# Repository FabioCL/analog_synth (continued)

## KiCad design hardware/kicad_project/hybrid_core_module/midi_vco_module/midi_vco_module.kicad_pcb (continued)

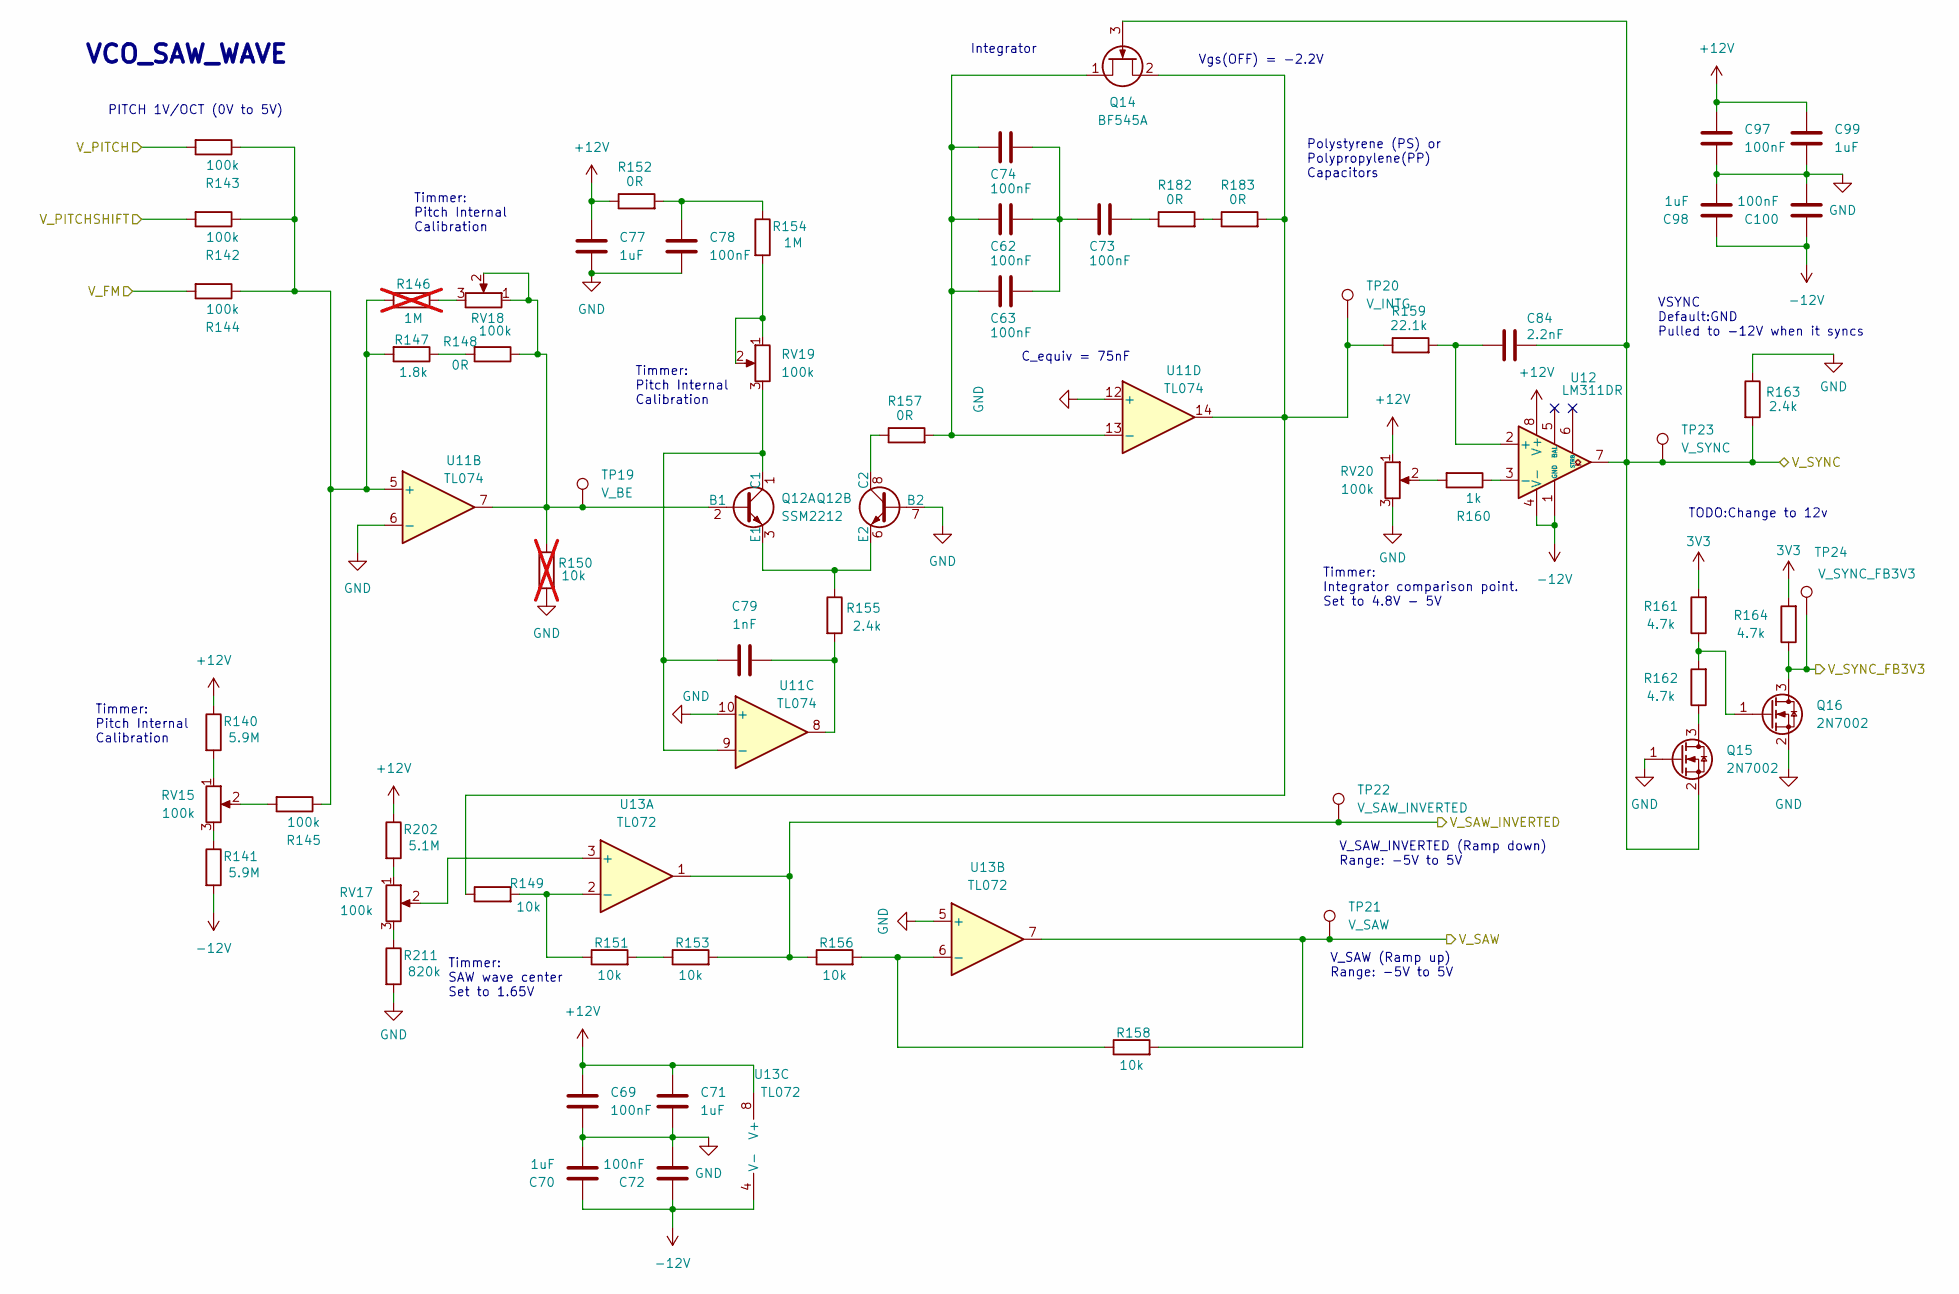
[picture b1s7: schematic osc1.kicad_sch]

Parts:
C62, C63, C73, C74: 100nF; C_1206_3216Metric; Manufacturer PartNumer GRT31C5C1H104FA02L
C69, C72, C78, C97, C100: 100nF; C_0402_1005Metric; Manufacturer PartNumer GRM155R71E104KE14J
C70, C71, C77, C98, C99: 1uF; C_0805_2012Metric; Manufacturer PartNumer GRM219R71E105MA88J
C79: 1nF; C_0402_1005Metric; Manufacturer PartNumer GRM155R71E103KA01J
C84: 2.2nF; C_0402_1005Metric; Manufacturer PartNumer GRM155R71H222KA01J
Q12: SSM2212; JEITA_SOIC-8_3.9x4.9mm_P1.27mm; Manufacturer PartNumer SSM2212RZ
Q14: BF545A; SOT-23; Manufacturer PartNumer MMBFJ108
Q15, Q16: 2N7002; SOT-23; Manufacturer PartNumer 2N7002
R140, R141: 5.9M; R_0402_1005Metric; Manufacturer PartNumer RC0402FR-075M9L
R142, R143, R144, R145: 100k; R_0402_1005Metric; Manufacturer PartNumer RT0402FRE07100KL
R146: 1M; R_0402_1005Metric; Manufacturer PartNumer RE0402BRE071ML; not fitted
R147: 1.8k; R_0402_1005Metric; Manufacturer PartNumer RT0402BRE071K8L
R148, R152, R157: 0R; R_0402_1005Metric; Manufacturer PartNumer RC0402FR-070RL
R149, R151, R153, R156, R158: 10k; R_0402_1005Metric; Manufacturer PartNumer RT0402FRE0710KL
R150: 10k; R_0402_1005Metric; Manufacturer PartNumer RT0402FRE0710KL; not fitted
R154: 1M; R_0402_1005Metric; Manufacturer PartNumer RE0402BRE071ML
R155, R163: 2.4k; R_0402_1005Metric; Manufacturer PartNumer RT0402BRD072K4L
R159: 22.1k; R_0402_1005Metric; Manufacturer PartNumer RT0402FRE0721KL
R160: 1k; R_0402_1005Metric; Manufacturer PartNumer RT0402FRE071KL
R161, R162, R164: 4.7k; R_0402_1005Metric; Manufacturer PartNumer RT0402FRE074K7L
R182, R183: 0R; R_1206_3216Metric; Manufacturer PartNumer RC0402FR-070RL
R202: 5.1M; R_0402_1005Metric; Manufacturer PartNumer RC0402FR-075M1L
R211: 820k; R_0402_1005Metric; Manufacturer PartNumer RC0402FR-07820KL
RV15, RV17, RV20: 100k; Potentiometer_Bourns_3296W_Vertical; Manufacturer PartNumer 3296W-104-LF
RV18, RV19: 100k; Potentiometer_Bourns_3296W_Vertical; Manufacturer PartNumer RT0402FRE07100KL
TP19: V_BE; TestPoint_Pad_1.0x1.0mm
TP20: V_INTG; TestPoint_Pad_1.0x1.0mm
TP21: V_SAW; TestPoint_Pad_1.0x1.0mm
TP22: V_SAW_INVERTED; TestPoint_Pad_1.0x1.0mm
TP23: V_SYNC; TestPoint_Pad_1.0x1.0mm
TP24: V_SYNC_FB3V3; TestPoint_Pad_1.0x1.0mm
U11: TL074; SOIC-14_3.9x8.7mm_P1.27mm; Manufacturer PartNumer TL074HIDR
U12: LM311DR; SOIC-8_5.3x6.2mm_P1.27mm; Manufacturer PartNumer LM311DR
U13: TL072; SOIC-8_5.3x6.2mm_P1.27mm; Manufacturer PartNumer TL072CDR

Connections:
3V3: R161.2, R164.2; also elsewhere on the board
+12V: C69.1, C71.1, C77.1, C97.1, C99.1, R140.1, R152.1, R202.1, RV20.1, U12.8 (V+), U13.8 (V+); also elsewhere on the board
-12V: C70.1, C72.1, C98.1, C100.1, R141.2, U12.1 (GND), U12.4 (V-), U13.4 (V-); also elsewhere on the board
/MCU/OSC1_FB: Q16.3 (D), R164.1, TP24.1; also elsewhere on the board
/SAW_PULSE_A/V_SAW: R158.2, TP21.1, U13.7; also elsewhere on the board
/SAW_TRIANG_A/V_SAW_INVERTED: R153.2, R156.1, TP22.1, U13.1; also elsewhere on the board
/SYNTH_CV/CTRL_PITCH_OSC1: R143.2; also elsewhere on the board
/VCO_SAW_A/V_FM: R144.2; also elsewhere on the board
/VCO_SAW_A/V_PITCHSHIFT: R142.2; also elsewhere on the board
/VCO_SAW_A/V_SYNC: C84.1, Q14.3 (G), Q15.2 (S), R163.2, TP23.1, U12.7; also elsewhere on the board
GND: C69.2, C70.2, C71.2, C72.2, C77.2, C78.2, C97.2, C98.2, C99.2, C100.2, Q12.7 (B2), Q15.1 (G), Q16.2 (S), R150.2, R163.1, R211.2, RV20.3, U11.6 (-), U11.10 (+), U11.12 (+), U13.5 (+); also elsewhere on the board
unnamed: C62.1, C63.1, C73.2, C74.1
unnamed: C73.1, R182.1
unnamed: C78.1, R152.2, R154.1
unnamed: C79.2, R155.2, U11.8
unnamed: Q12.2 (B1), R148.1, R150.1, RV18.1, RV18.2, TP19.1, U11.7
unnamed: C79.1, Q12.1 (C1), RV19.3, U11.9 (-)
unnamed: Q12.3 (E1), Q12.6 (E2), R155.1
unnamed: Q12.8 (C2), R157.1
unnamed: Q14.2 (D), R149.1, R159.1, R183.2, TP20.1, U11.14
unnamed: C62.2, C63.2, C74.2, Q14.1 (S), R157.2, U11.13 (-)
unnamed: Q15.3 (D), R162.1
unnamed: Q16.1 (G), R161.1, R162.2
unnamed: R140.2, RV15.1
unnamed: R141.1, RV15.3
unnamed: R145.2, RV15.2
unnamed: R146.1, RV18.3
unnamed: R147.1, R148.2
unnamed: R151.2, R153.1
unnamed: R154.2, RV19.1, RV19.2
unnamed: R160.2, RV20.2
unnamed: R182.2, R183.1
unnamed: R202.2, RV17.1
unnamed: R211.1, RV17.3
unnamed: R142.1, R143.1, R144.1, R145.1, R146.2, R147.2, U11.5 (+)
unnamed: C84.2, R159.2, U12.2 (+)
unnamed: R160.1, U12.3 (-)
unnamed: RV17.2, U13.3 (+)
unnamed: R149.2, R151.1, U13.2 (-)
unnamed: R156.2, R158.1, U13.6 (-)

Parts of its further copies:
C44, C47, C53, C101, C104: 100nF; C_0402_1005Metric; Manufacturer PartNumer GRM155R71E104KE14J
C45, C46, C52, C102, C103: 1uF; C_0805_2012Metric; Manufacturer PartNumer GRM219R71E105MA88J
C54: 1nF; C_0402_1005Metric; Manufacturer PartNumer GRM155R71E103KA01J
C55, C56, C57, C58: 100nF; C_1206_3216Metric; Manufacturer PartNumer GRT31C5C1H104FA02L
C59: 2.2nF; C_0402_1005Metric; Manufacturer PartNumer GRM155R71H222KA01J
Q6: SSM2212; JEITA_SOIC-8_3.9x4.9mm_P1.27mm; Manufacturer PartNumer SSM2212RZ
Q8: BF545A; SOT-23; Manufacturer PartNumer MMBFJ108
Q9, Q10: 2N7002; SOT-23; Manufacturer PartNumer 2N7002
R70, R71: 5.9M; R_0402_1005Metric; Manufacturer PartNumer RC0402FR-075M9L
R72, R73, R74, R75: 100k; R_0402_1005Metric; Manufacturer PartNumer RT0402FRE07100KL
R76: 1M; R_0402_1005Metric; Manufacturer PartNumer RE0402BRE071ML; not fitted
R77: 1.8k; R_0402_1005Metric; Manufacturer PartNumer RT0402BRE071K8L
R78, R82, R87: 0R; R_0402_1005Metric; Manufacturer PartNumer RC0402FR-070RL
R79, R81, R83, R86, R88: 10k; R_0402_1005Metric; Manufacturer PartNumer RT0402FRE0710KL
R80: 10k; R_0402_1005Metric; Manufacturer PartNumer RT0402FRE0710KL; not fitted
R84: 1M; R_0402_1005Metric; Manufacturer PartNumer RE0402BRE071ML
R85, R93: 2.4k; R_0402_1005Metric; Manufacturer PartNumer RT0402BRD072K4L
R89: 22.1k; R_0402_1005Metric; Manufacturer PartNumer RT0402FRE0721KL
R90: 1k; R_0402_1005Metric; Manufacturer PartNumer RT0402FRE071KL
R91, R92, R94: 4.7k; R_0402_1005Metric; Manufacturer PartNumer RT0402FRE074K7L
R180, R181: 0R; R_1206_3216Metric; Manufacturer PartNumer RC0402FR-070RL
R205: 5.1M; R_0402_1005Metric; Manufacturer PartNumer RC0402FR-075M1L
R212: 820k; R_0402_1005Metric; Manufacturer PartNumer RC0402FR-07820KL
RV2, RV4, RV7: 100k; Potentiometer_Bourns_3296W_Vertical; Manufacturer PartNumer 3296W-104-LF
RV5, RV6: 100k; Potentiometer_Bourns_3296W_Vertical; Manufacturer PartNumer RT0402FRE07100KL
TP9: V_BE; TestPoint_Pad_1.0x1.0mm
TP10: V_INTG; TestPoint_Pad_1.0x1.0mm
TP11: V_SAW; TestPoint_Pad_1.0x1.0mm
TP12: V_SAW_INVERTED; TestPoint_Pad_1.0x1.0mm
TP13: V_SYNC; TestPoint_Pad_1.0x1.0mm
TP14: V_SYNC_FB3V3; TestPoint_Pad_1.0x1.0mm
U22: LM311DR; SOIC-8_5.3x6.2mm_P1.27mm; Manufacturer PartNumer LM311DR
U23: TL072; SOIC-8_5.3x6.2mm_P1.27mm; Manufacturer PartNumer TL072CDR

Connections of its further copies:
3V3: R91.2, R94.2; also elsewhere on the board
+12V: C44.1, C46.1, C52.1, C101.1, C103.1, R70.1, R82.1, R205.1, RV7.1, U22.8 (V+), U23.8 (V+); also elsewhere on the board
-12V: C45.1, C47.1, C102.1, C104.1, R71.2, U22.1 (GND), U22.4 (V-), U23.4 (V-); also elsewhere on the board
/MCU/OSC2_FB: Q10.3 (D), R94.1, TP14.1; also elsewhere on the board
/SAW_PULSE_B/V_SAW: R88.2, TP11.1, U23.7; also elsewhere on the board
/SAW_TRIANG_B/V_SAW_INVERTED: R83.2, R86.1, TP12.1, U23.1; also elsewhere on the board
/SYNTH_CV/CTRL_PITCH_OSC2: R73.2; also elsewhere on the board
/VCO_SAW_A/V_FM: R74.2; also elsewhere on the board
/VCO_SAW_B/V_PITCHSHIFT: R72.2; also elsewhere on the board
/VCO_SAW_B/V_SYNC: C59.1, Q8.3 (G), Q9.2 (S), R93.2, TP13.1, U22.7; also elsewhere on the board
GND: C44.2, C45.2, C46.2, C47.2, C52.2, C53.2, C101.2, C102.2, C103.2, C104.2, Q6.7 (B2), Q9.1 (G), Q10.2 (S), R80.2, R93.1, R212.2, RV7.3, U23.5 (+); also elsewhere on the board
unnamed: C53.1, R82.2, R84.1
unnamed 97: C54.2, R85.2; also elsewhere on the board
unnamed: C55.1, C56.1, C57.2, C58.1
unnamed: C57.1, R180.1
unnamed 149: Q6.2 (B1), R78.1, R80.1, RV5.1, RV5.2, TP9.1; also elsewhere on the board
unnamed 150: C54.1, Q6.1 (C1), RV6.3; also elsewhere on the board
unnamed: Q6.3 (E1), Q6.6 (E2), R85.1
unnamed: Q6.8 (C2), R87.1
unnamed 154: Q8.2 (D), R79.1, R89.1, R181.2, TP10.1; also elsewhere on the board
unnamed 155: C55.2, C56.2, C58.2, Q8.1 (S), R87.2; also elsewhere on the board
unnamed: Q9.3 (D), R92.1
unnamed: Q10.1 (G), R91.1, R92.2
unnamed: R70.2, RV2.1
unnamed: R71.1, RV2.3
unnamed: R75.2, RV2.2
unnamed: R76.1, RV5.3
unnamed: R77.1, R78.2
unnamed: R81.2, R83.1
unnamed: R84.2, RV6.1, RV6.2
unnamed: R90.2, RV7.2
unnamed: R180.2, R181.1
unnamed: R205.2, RV4.1
unnamed: R212.1, RV4.3
unnamed 262: R72.1, R73.1, R74.1, R75.1, R76.2, R77.2; also elsewhere on the board
unnamed: C59.2, R89.2, U22.2 (+)
unnamed: R90.1, U22.3 (-)
unnamed: RV4.2, U23.3 (+)
unnamed: R79.2, R81.1, U23.2 (-)
unnamed: R86.2, R88.1, U23.6 (-)

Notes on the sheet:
Timmer: SAW wave center Set to 1.65V
TODO:Change to 12v
VSYNC Default:GND Pulled to -12V when it syncs
Polystyrene (PS) or Polypropylene(PP) Capacitors
Timmer: Pitch Internal Calibration
Integrator
C_equiv = 75nF
PITCH 1V/OCT (0V to 5V)
V_SAW_INVERTED (Ramp down) Range: -5V to 5V
Timmer: Integrator comparison point. Set to 4.8V - 5V
VCO_SAW_WAVE
V_SAW (Ramp up) Range: -5V to 5V
Vgs(OFF) = -2.2V

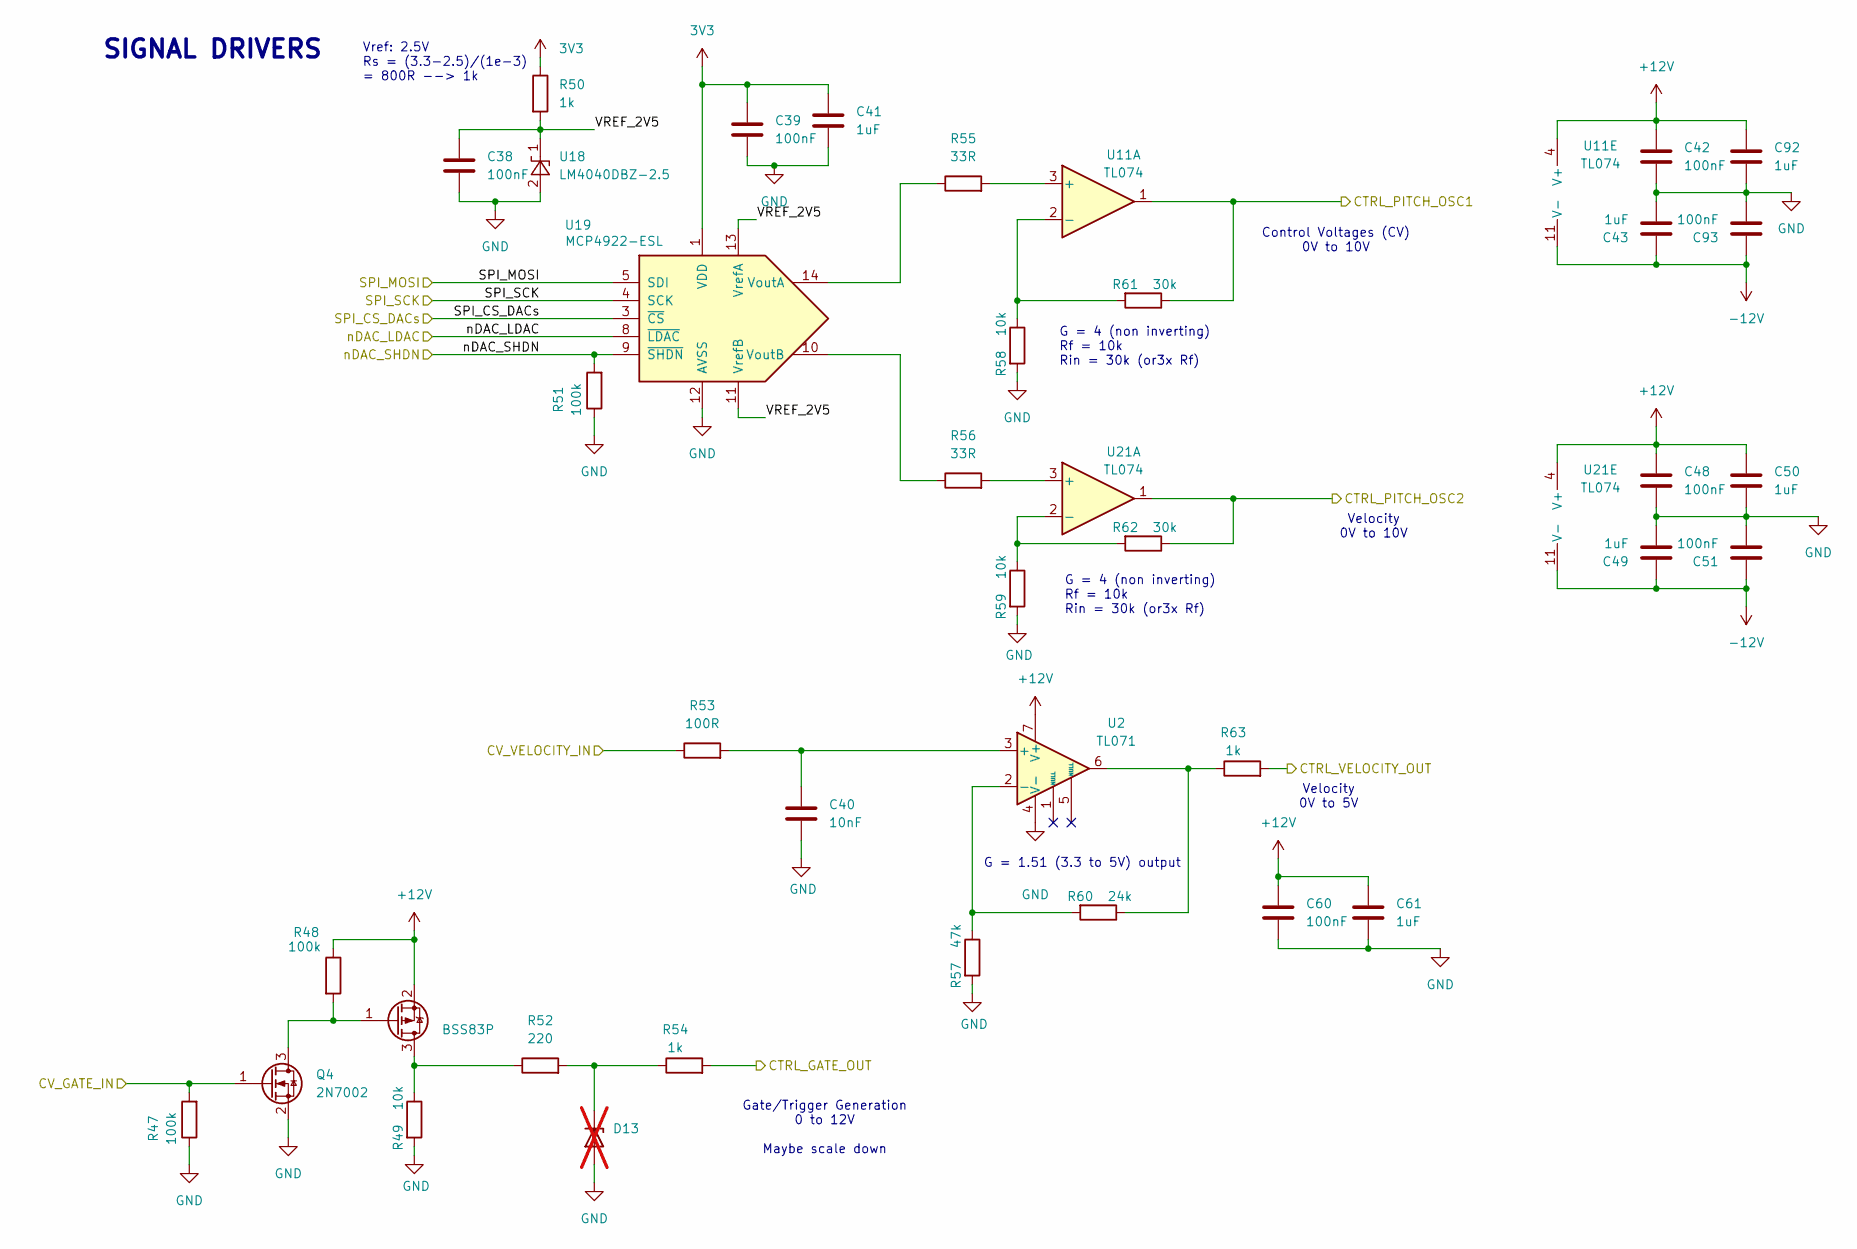
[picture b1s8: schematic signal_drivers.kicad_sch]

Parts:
C38, C39, C42, C48, C51, C60, C93: 100nF; C_0402_1005Metric; Manufacturer PartNumer GRM155R71E104KE14J
C40: 10nF; C_0402_1005Metric; Manufacturer PartNumer GRM155R71E103KA01D
C41, C43, C49, C50, C61, C92: 1uF; C_0805_2012Metric; Manufacturer PartNumer GRM219R71E105MA88J
D13: BZT52Bxx; D_SOD-123F; Manufacturer PartNumer BZT52-B10J; not fitted
Q4: 2N7002; SOT-23; Manufacturer PartNumer 2N7002
Q5: BSS83P; SOT-23; Manufacturer PartNumer BSS83PH6327XTSA1
R47, R48, R51: 100k; R_0402_1005Metric; Manufacturer PartNumer RT0402FRE07100KL
R49, R58, R59: 10k; R_0402_1005Metric; Manufacturer PartNumer RT0402FRE0710KL
R50, R54, R63: 1k; R_0402_1005Metric; Manufacturer PartNumer RT0402FRE071KL
R52: 220; R_0402_1005Metric; Manufacturer PartNumer RT0402FRE07220RL
R53: 100R; R_0402_1005Metric; Manufacturer PartNumer RT0402FRE07100RL
R55, R56: 33R; R_0402_1005Metric; Manufacturer PartNumer RT0402FRE0733RL
R57: 47k; R_0402_1005Metric; Manufacturer PartNumer RT0402FRE0747KL
R60: 24k; R_0402_1005Metric; Manufacturer PartNumer RT0402FRE0724KL
R61, R62: 30k; R_0402_1005Metric; Manufacturer PartNumer RT0402FRE0730KL
U2: TL071; SOIC-8_3.9x4.9mm_P1.27mm; Manufacturer PartNumer TL071CDR
U11, U21: TL074; SOIC-14_3.9x8.7mm_P1.27mm; Manufacturer PartNumer TL074HIDR
U18: LM4040DBZ-2.5; SOT-23; Manufacturer PartNumer LM4040QAIM3-2.5/NOPB
U19: MCP4922-ESL; SOIC-14_3.9x8.7mm_P1.27mm; Manufacturer PartNumer MCP4922-E/SL

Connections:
3V3: C39.1, C41.1, R50.1, U19.1 (VDD); also elsewhere on the board
+12V: C42.1, C48.1, C50.1, C60.1, C61.1, C92.1, Q5.2 (S), R48.1, U2.7 (V+), U11.4 (V+), U21.4 (V+); also elsewhere on the board
-12V: C43.1, C49.1, C51.1, C93.1, U11.11 (V-), U21.11 (V-); also elsewhere on the board
/MCU/CV_VELOCITY_DAC: R53.1; also elsewhere on the board
/MCU/ESP_GPIO04: R51.2, U19.9 (~SHDN); also elsewhere on the board
/MCU/ESP_GPIO05: U19.8 (~LDAC); also elsewhere on the board
/MCU/ESP_GPIO12: Q4.1 (G), R47.2; also elsewhere on the board
/MCU/ESP_GPIO15: U19.3 (~CS); also elsewhere on the board
/SYNTH_CV/CTRL_GATE_OUT: R54.2; also elsewhere on the board
/SYNTH_CV/CTRL_PITCH_OSC1: R61.1, U11.1; also elsewhere on the board
/SYNTH_CV/CTRL_PITCH_OSC2: R62.1, U21.1; also elsewhere on the board
/SYNTH_CV/CTRL_VELOCITY_OUT: R63.2; also elsewhere on the board
/SYNTH_CV/SPI_MOSI: U19.5 (SDI); also elsewhere on the board
/SYNTH_CV/SPI_SCK: U19.4 (SCK); also elsewhere on the board
/SYNTH_CV/VREF_2V5: C38.1, R50.2, U18.1 (K), U19.11 (VrefB), U19.13 (VrefA)
GND: C38.2, C39.2, C40.2, C41.2, C42.2, C43.2, C48.2, C49.2, C50.2, C51.2, C60.2, C61.2, C92.2, C93.2, D13.2 (A), Q4.2 (S), R47.1, R49.2, R51.1, R57.2, R58.2, R59.2, U2.4 (V-), U18.2 (A), U19.12 (AVSS); also elsewhere on the board
unnamed: D13.1 (K), R52.2, R54.1
unnamed: Q4.3 (D), Q5.1 (G), R48.2
unnamed: Q5.3 (D), R49.1, R52.1
unnamed: R60.1, R63.1, U2.6
unnamed: C40.1, R53.2, U2.3 (+)
unnamed: R57.1, R60.2, U2.2 (-)
unnamed: R55.2, U11.3 (+)
unnamed: R58.1, R61.2, U11.2 (-)
unnamed: R55.1, U19.14 (VoutA)
unnamed: R56.1, U19.10 (VoutB)
unnamed: R56.2, U21.3 (+)
unnamed: R59.1, R62.2, U21.2 (-)

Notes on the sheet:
Velocity 0V to 5V
G = 4 (non inverting) Rf = 10k Rin = 30k (or3x Rf)
G = 1.51 (3.3 to 5V) output
Gate/Trigger Generation 0 to 12V Maybe scale down
Control Voltages (CV) 0V to 10V
Velocity 0V to 10V
Vref: 2.5V Rs = (3.3-2.5)/(1e-3) = 800R --> 1k
SIGNAL DRIVERS

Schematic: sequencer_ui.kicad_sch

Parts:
C67, C95: 100nF; C_0402_1005Metric; Manufacturer PartNumer GRM155R71E104KE14J
C68, C96: 1uF; C_0805_2012Metric; Manufacturer PartNumer GRM219R71E105MA88J
C76, C80, C81, C82, C83, C85, C86, C87, C88, C94, C105: 1nF; C_0402_1005Metric; Manufacturer PartNumer GRM155R71E103KA01J
D16, D17, D18, D19, D20, D21, D22, D23, D24, D25, D26, D27, D28, D29, D30, D31: LED; LED_D3.0mm_Clear; Manufacturer PartNumer ORANGE LED 3MM
J11, J12, J13, J14, J15, J16, J17, J18, J19, J20, J21, J22: Conn_01x01_Pin; PinHeader_1x01_P1.00mm_Vertical; not fitted
Q18, Q19, Q20: 2N7002; SOT-23; Manufacturer PartNumer 2N7002
R109, R110, R111, R115, R116, R117, R190, R201, R208, R209, R210: 100k; R_0402_1005Metric; Manufacturer PartNumer RT0402FRE07100KL
R112, R114, R185, R187, R198: 4.7k; R_0402_1005Metric; Manufacturer PartNumer RT0402FRE074K7L
R113, R139, R175, R176, R192, R193, R194, R195, R197: 100R; R_0402_1005Metric; Manufacturer PartNumer RT0402FRE07100RL
R118, R199: 0R; R_0402_1005Metric; Manufacturer PartNumer RC0402FR-070RL; not fitted
R119, R200: 0R; R_0402_1005Metric; Manufacturer PartNumer RC0402FR-070RL
R120, R121, R122, R123, R124, R125, R126, R127, R128, R129, R130, R131, R132, R133, R134, R135: 470; R_0402_1005Metric; Manufacturer PartNumer RT0402FRE07470RL
R138, R189: 10k; R_0402_1005Metric; Manufacturer PartNumer RT0402FRE0710KL
RV13: 100k; Potentiometer_RV09_Single_Vertical; Manufacturer PartNumer 3296W-104-LF
SW9: SW_Rotary_1x4_MP; SR16 Rotary Band Switch; Manufacturer PartNumer SR16
SW10, SW11: RotaryEncoder_Switch_MP; RotaryEncoder_Alps_EC11E-Switch_Vertical_H20mm_CircularMoun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
U15: MCP23008-xSO; SOIC-18W_7.5x11.6mm_P1.27mm; Manufacturer PartNumer MCP23008T-E/SO
U25: MCP23017_SO; SOIC-28W_7.5x17.9mm_P1.27mm; Manufacturer PartNumer MCP23017-E/SO

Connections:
3V3: C67.1, C68.1, C95.1, C96.1, D16.2 (A), D17.2 (A), D18.2 (A), D19.2 (A), D20.2 (A), D21.2 (A), D22.2 (A), D23.2 (A), D24.2 (A), D25.2 (A), D26.2 (A), D27.2 (A), D28.2 (A), D29.2 (A), D30.2 (A), D31.2 (A), R109.2, R110.2, R111.2, R112.2, R114.2, R118.2, R138.2, R185.2, R187.2, R189.2, R190.2, R198.2, R200.2, RV13.1, SW9.1, U15.3 (A2), U15.4 (A1), U15.18 (VDD), U25.9 (VDD); also elsewhere on the board
/MCU/I2C_SCL: U15.1 (SCL), U25.12 (SCK); also elsewhere on the board
/MCU/I2C_SDA: U15.2 (SDA), U25.13 (SDA); also elsewhere on the board
/MCU/MCP2_INT: R198.1, U15.8 (INT); also elsewhere on the board
/MCU/MCP2_RST: R201.2, U15.6 (~RESET); also elsewhere on the board
/MCU/SEQ_CLK_A: C86.2, R175.1; also elsewhere on the board
/MCU/SEQ_CLK_B: C87.2, R176.1; also elsewhere on the board
/MCU/SEQ_DIRECTION_IN: C83.2, R113.1; also elsewhere on the board
/MCU/SEQ_GATE_LENGTH_IN: C105.2, R139.1; also elsewhere on the board
/MCU/SEQ_STEPS_A: C81.2, R194.1; also elsewhere on the board
/MCU/SEQ_STEPS_B: C82.2, R195.1; also elsewhere on the board
/SEQUENCER_UI/BT_REC_LED: Q20.1 (G), R210.2, U15.17 (GP7)
/SEQUENCER_UI/BT_REC_OUT: C80.2, R193.1, U15.16 (GP6)
/SEQUENCER_UI/BT_START_LED: Q18.1 (G), R208.2, U15.15 (GP5)
/SEQUENCER_UI/BT_START_OUT: C76.2, R192.1, U15.14 (GP4)
/SEQUENCER_UI/BT_STOP_LED: Q19.1 (G), R209.2, U15.13 (GP3)
/SEQUENCER_UI/BT_STOP_OUT: C94.2, R197.1, U15.12 (GP2)
/SEQUENCER_UI/LED1: R120.1, U25.1 (GPB0)
/SEQUENCER_UI/LED2: R122.1, U25.2 (GPB1)
/SEQUENCER_UI/LED3: R124.1, U25.3 (GPB2)
/SEQUENCER_UI/LED4: R126.1, U25.4 (GPB3)
/SEQUENCER_UI/LED5: R128.1, U25.5 (GPB4)
/SEQUENCER_UI/LED6: R130.1, U25.6 (GPB5)
/SEQUENCER_UI/LED7: R132.1, U25.7 (GPB6)
/SEQUENCER_UI/LED8: R134.1, U25.8 (GPB7)
/SEQUENCER_UI/LED9: R121.1, U25.28 (GPA7)
/SEQUENCER_UI/LED10: R123.1, U25.27 (GPA6)
/SEQUENCER_UI/LED11: R125.1, U25.26 (GPA5)
/SEQUENCER_UI/LED12: R127.1, U25.25 (GPA4)
/SEQUENCER_UI/LED13: R129.1, U25.24 (GPA3)
/SEQUENCER_UI/LED14: R131.1, U25.23 (GPA2)
/SEQUENCER_UI/LED15: R133.1, U25.22 (GPA1)
/SEQUENCER_UI/LED16: R135.1, U25.21 (GPA0)
/SEQUENCER_UI/MCP_RST: R117.2, U25.18 (~RESET); also elsewhere on the board
/SEQUENCER_UI/SEQ_CLK_SW: C88.2, R189.1, SW10.S1, U15.10 (GP0)
/SEQUENCER_UI/SEQ_STEPS_SW: C85.2, R138.1, SW11.S1, U15.11 (GP1)
GND: C67.2, C68.2, C76.1, C80.1, C81.1, C82.1, C83.1, C85.1, C86.1, C87.1, C88.1, C94.1, C95.2, C96.2, C105.1, J12.1, J14.1, J16.1, Q18.2 (S), Q19.2 (S), Q20.2 (S), R116.1, R117.1, R119.1, R199.1, R201.1, R208.1, R209.1, R210.1, RV13.3, SW9.4, SW9.MP, SW10.C, SW10.MP, SW10.S2, SW11.C, SW11.MP, SW11.S2, U15.9 (VSS), U25.10 (VSS), U25.15 (A0), U25.16 (A1); also elsewhere on the board
unnamed: D16.1 (K), R120.2
unnamed: D17.1 (K), R121.2
unnamed: D18.1 (K), R122.2
unnamed: D19.1 (K), R123.2
unnamed: D20.1 (K), R124.2
unnamed: D21.1 (K), R125.2
unnamed: D22.1 (K), R126.2
unnamed: D23.1 (K), R127.2
unnamed: D24.1 (K), R128.2
unnamed: D25.1 (K), R129.2
unnamed: D26.1 (K), R130.2
unnamed: D27.1 (K), R131.2
unnamed: D28.1 (K), R132.2
unnamed: D29.1 (K), R133.2
unnamed: D30.1 (K), R134.2
unnamed: D31.1 (K), R135.2
unnamed: J11.1, R109.1, R193.2
unnamed: J13.1, R110.1, R192.2
unnamed: J15.1, R111.1, R197.2
unnamed: J17.1, Q18.3 (D)
unnamed: J20.1, Q19.3 (D)
unnamed: J22.1, Q20.3 (D)
unnamed: R112.1, R195.2, SW11.B
unnamed: R113.2, SW9.5
unnamed: R114.1, R194.2, SW11.A
unnamed: R115.1, R116.2, SW9.3
unnamed: R115.2, R190.1, SW9.2
unnamed: R139.2, RV13.2
unnamed: R175.2, R187.1, SW10.A
unnamed: R176.2, R185.1, SW10.B
unnamed: R199.2, R200.1, U15.5 (A0)
unnamed: R118.1, R119.2, U25.17 (A2)
VIN_5V: J18.1, J19.1, J21.1; also elsewhere on the board

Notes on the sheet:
CLK FREQ (INCREASE DECREASE, based on click)
STOP Button
I2C ADDRESS: 0x27
REC Button (Record mode keep it pressed)
GATE LENGTH (Staccato - legatto)
I2C ADDRESS: 0x20
DIRECTION: Forward, Pingpong, Backward, Random
START Button
ROTARY STEPS (1 to 16+)
USE max 16* 1mA LEDs

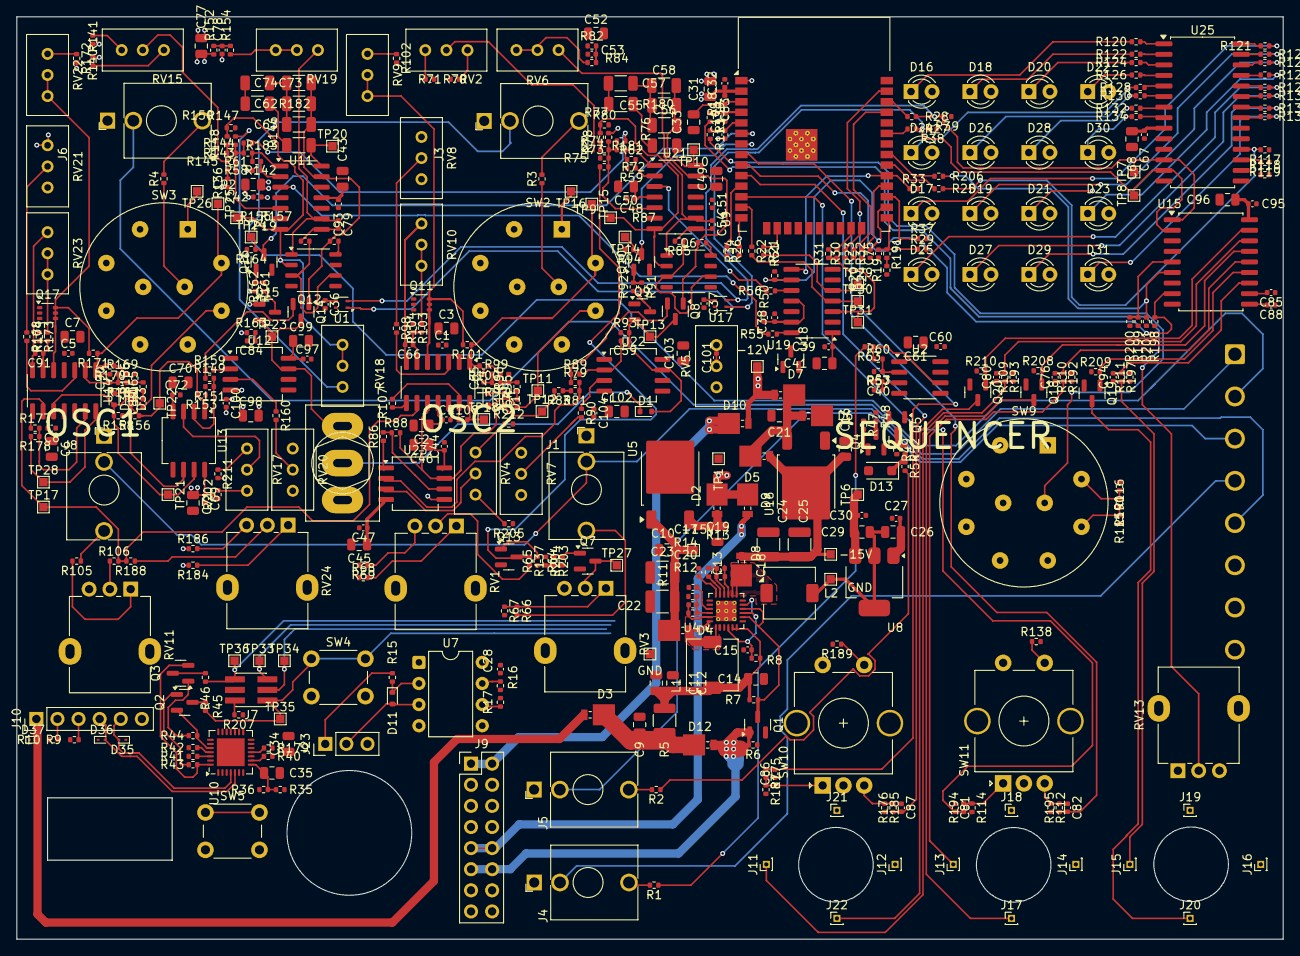
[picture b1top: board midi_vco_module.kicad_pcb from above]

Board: 4 copper layers, 152.4 x 111.0 mm, 484 parts (1 on the bottom side), 276 nets.

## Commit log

2025-08-27 added simulations as backup
2025-10-22 Added Hybrid core module
2025-10-26 Schematic updated. Components Footprint assignment started. Waiting for components mechanical validation before starting layout.
2025-11-10 - schematic updated - PN and footprints added
2025-11-11 components placement (interface) components placement per section
2025-11-14 - placement done - routing 60%
2025-11-15 routing continued.
